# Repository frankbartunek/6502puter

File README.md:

<h1>6502 Computer</h2>
<p>These schematics were made with KiCAD, and describe a single-board computer.</p>

<p>The computer uses a 6502 processor, a 6552 I/O chip, and should be able to accept a USB keyboard for input, and output to a VGA monitor.</p>

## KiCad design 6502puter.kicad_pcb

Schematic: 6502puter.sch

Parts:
C1, C5: CP1; CP_Radial_D4.0mm_P1.50mm
C2, C3: 4.7k; CP_Radial_D4.0mm_P1.50mm
C4: 10uF; CP_Radial_D4.0mm_P1.50mm
C6, C7: 10 uF; CP_Radial_Tantal_D4.5mm_P2.50mm
IC1: PIC24FV32KA304-IPT; TQFP-44_10x10mm_Pitch0.8mm
J1: DB15_Female; DB15FD
J2: DB9_Male; DB9MD
J3: Screw_Terminal_01x02; Molex_KK-6410-02_02x2.54mm_Straight
J4: Conn_01x06; Molex_KK-6410-06_06x2.54mm_Straight
J5: USB_A
R1, R2: 27k; R_Axial_DIN0204_L3.6mm_D1.6mm_P1.90mm_Vertical
R3: 5k; R_Axial_DIN0204_L3.6mm_D1.6mm_P1.90mm_Vertical
SW1: SW_Push; SW_DIP_x1_W7.62mm_Piano
U1: 6510; DIP-40_W15.24mm_Socket
U2: R6532; DIP-40_W15.24mm_Socket
U3: WD65C22; DIP-40_W15.24mm_Socket
U4: W65C51N; DIP-28_W15.24mm
U5: 74HC14; DIP-14_W7.62mm
U6: MAX232; DIP-16_W7.62mm_Socket
U7: 27C512PLCC; DIP-32_W15.24mm_Socket
U8: M29W004; DIP-40_W25.4mm_Socket
U9, U10: 74LS32; DIP-14_W7.62mm
U11: SN74LVC1G332; DIP-6_W7.62mm_Socket
U12: 74HC595; DIP-16_W7.62mm
U13: ATTINY13-20PU; DIP-8_W7.62mm
Y1: Crystal; Crystal_HC33-U_Vertical
Y2: Crystal_Small; Resonator-2pin_w6.0mm_h3.0mm

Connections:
+5V: C1.1, C5.2, IC1.17, IC1.28, IC1.40, J3.1, J5.1, SW1.1, U1.6, U2.20, U3.20, U4.15, U5.14 (VCC), U6.16, U7.32, U8.30, U8.31, U9.14, U10.14, U11.5, U12.16, U13.8
ACIA0: U1.14, U4.13
ACIACS: U4.2
BYTEREADY: U3.40, U13.3
Blue: IC1.23, J1.3
CPUA0: U1.7, U8.21, U9.4
CPUA1: U1.8, U8.20, U9.5
CPUA2: U1.9, U8.19, U9.10
CPUA3: U1.10, U8.18, U9.9
CPUA4: U1.11, U8.17, U9.12
CPUA5: U1.12
CPUA6: U1.13, U3.38
CPUA8: U1.15, U2.7
CPUA9: U1.16
CPUA10: U1.17
CPUA11: U1.18, U7.11, U10.4
CPUA12: U1.19, U7.10, U10.5
CPUA13: U1.20, U7.9, U10.9
CPUA14: U1.22, U7.8, U10.10
CPUA15: U1.23, U7.7, U10.12
CTS: J2.8
D0: U1.37, U2.33, U3.33, U4.18, U7.13, U8.25
D1: U1.36, U2.32, U3.32, U4.19, U7.14, U8.26
D2: U1.35, U2.31, U3.31, U4.20, U7.15, U8.27
D3: U1.34, U2.30, U3.30, U4.21, U7.18, U8.28
D4: U1.33, U2.29, U3.29, U4.22, U7.19, U8.32
D5: U1.32, U2.28, U3.28, U4.23, U7.20, U8.33
D6: U1.31, U2.27, U3.27, U4.24, U7.21, U8.34
D7: U1.30, U2.26, U3.26, U4.25, U7.22, U8.35
DCD: J2.1
DSR: J2.6
DTR: J2.4
GND: C4.1, C6.2, C7.2, IC1.16, IC1.29, IC1.39, J1.5, J1.10, J2.5, J3.2, J4.3, J5.4, J5.5, R1.1, U1.21, U2.1, U3.1, U4.1, U5.7 (GND), U6.15, U7.16, U8.23, U8.39, U9.7, U10.7, U11.2, U12.8, U12.13, U13.4
Green: IC1.22, J1.2, J4.5
Hsync: IC1.24, J1.13, J4.6
ICSPDAT: IC1.21, J1.1, J4.4
INPUTA: U3.2, U12.15
INPUTB: U3.3, U12.1
INPUTC: U3.4, U12.2
INPUTD: U3.5, U12.3
INPUTE: U3.6, U12.4
INPUTF: U3.7, U12.5
INPUTG: U3.8, U12.6
INPUTH: U3.9, U12.7
IRQ: U1.3
MCLR: IC1.18, J4.1
Mainclock: U1.1
NMI: U1.4
unnamed: C1.2, R2.1, R3.2
unnamed: C2.1, U6.1
unnamed: C2.2, U6.3
unnamed: C3.1, U6.4
unnamed: C3.2, U6.5
unnamed: C4.2, U6.6
unnamed: C5.1, U6.2
unnamed: C6.1, IC1.31, Y1.2
unnamed: C7.1, IC1.30, Y1.1
unnamed: J5.2, U13.6
unnamed: J5.3, U13.5
unnamed: R1.2, R2.2, SW1.2
unnamed: R3.1, U5.1
unnamed: U4.6, Y2.1
unnamed: U4.7, Y2.2
unnamed: U9.1, U9.8
unnamed: U9.2, U9.6
unnamed: U9.11, U10.1
unnamed: U9.3, U10.2
unnamed: U10.6, U11.1
unnamed: U10.8, U11.3
unnamed: U10.11, U11.6
unnamed: U12.11, U12.12, U13.2
unnamed: U12.14, U13.7
PHI2: U1.39, U2.39, U3.25, U4.27, U9.13, U10.13
PWR: J4.2
RAMA5: U8.16
RAMA6: U8.15
RAMA7: U8.14
RAMA8: U8.8
RAMA9: U8.9
RAMA10: U8.36
RAMA11: U8.6
RAMA12: U8.5
RAMA13: U8.4
RAMA14: U8.3
RAMA15: U8.2
RAMA16: U8.1
RAMA17: U8.40
RAMA18: U8.13
RAMCS: U8.22, U10.3
RAMOE: U8.24
RI: J2.9
RIOTCS: U2.38
RIn: U4.12, U6.13
ROMA5: U7.6
ROMA6: U7.5
ROMA7: U7.4
ROMCS: U7.23, U11.4
ROMOE: U7.25
RTS: J2.7
RX: J2.2, U6.12
Reset: U1.40, U2.34, U3.34, U4.4, U5.2
TOut: U4.10, U6.14
TX: J2.3, U6.11
VIACS: U3.24
Vsync: IC1.33, J1.14

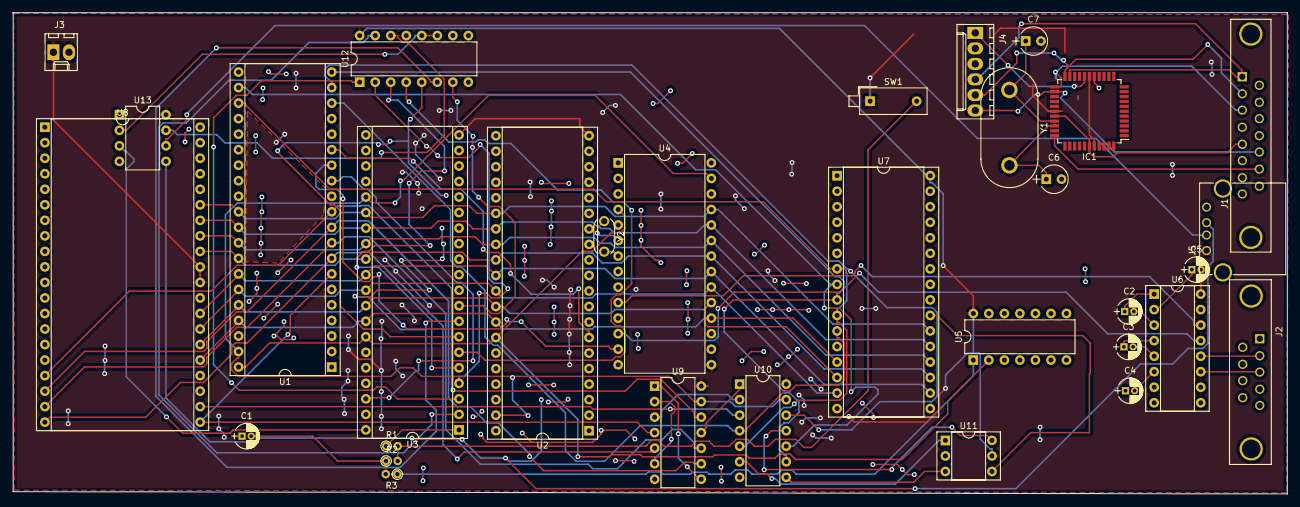
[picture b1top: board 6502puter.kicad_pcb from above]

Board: 2 copper layers, 208.5 x 78.7 mm, 32 parts (0 on the bottom side), 70 nets.

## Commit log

2018-12-19 File found to be in incorrect format
    Replacing file with correct format.
2018-12-19 Cached file included accidentally
    Purging file, file '6502puter.kicad_pcb' is the correct file for the information.
2019-04-23 README file properly formatted and added
    README was found to be previously improperly formatted, was fixed, and ordered immediately committed.
